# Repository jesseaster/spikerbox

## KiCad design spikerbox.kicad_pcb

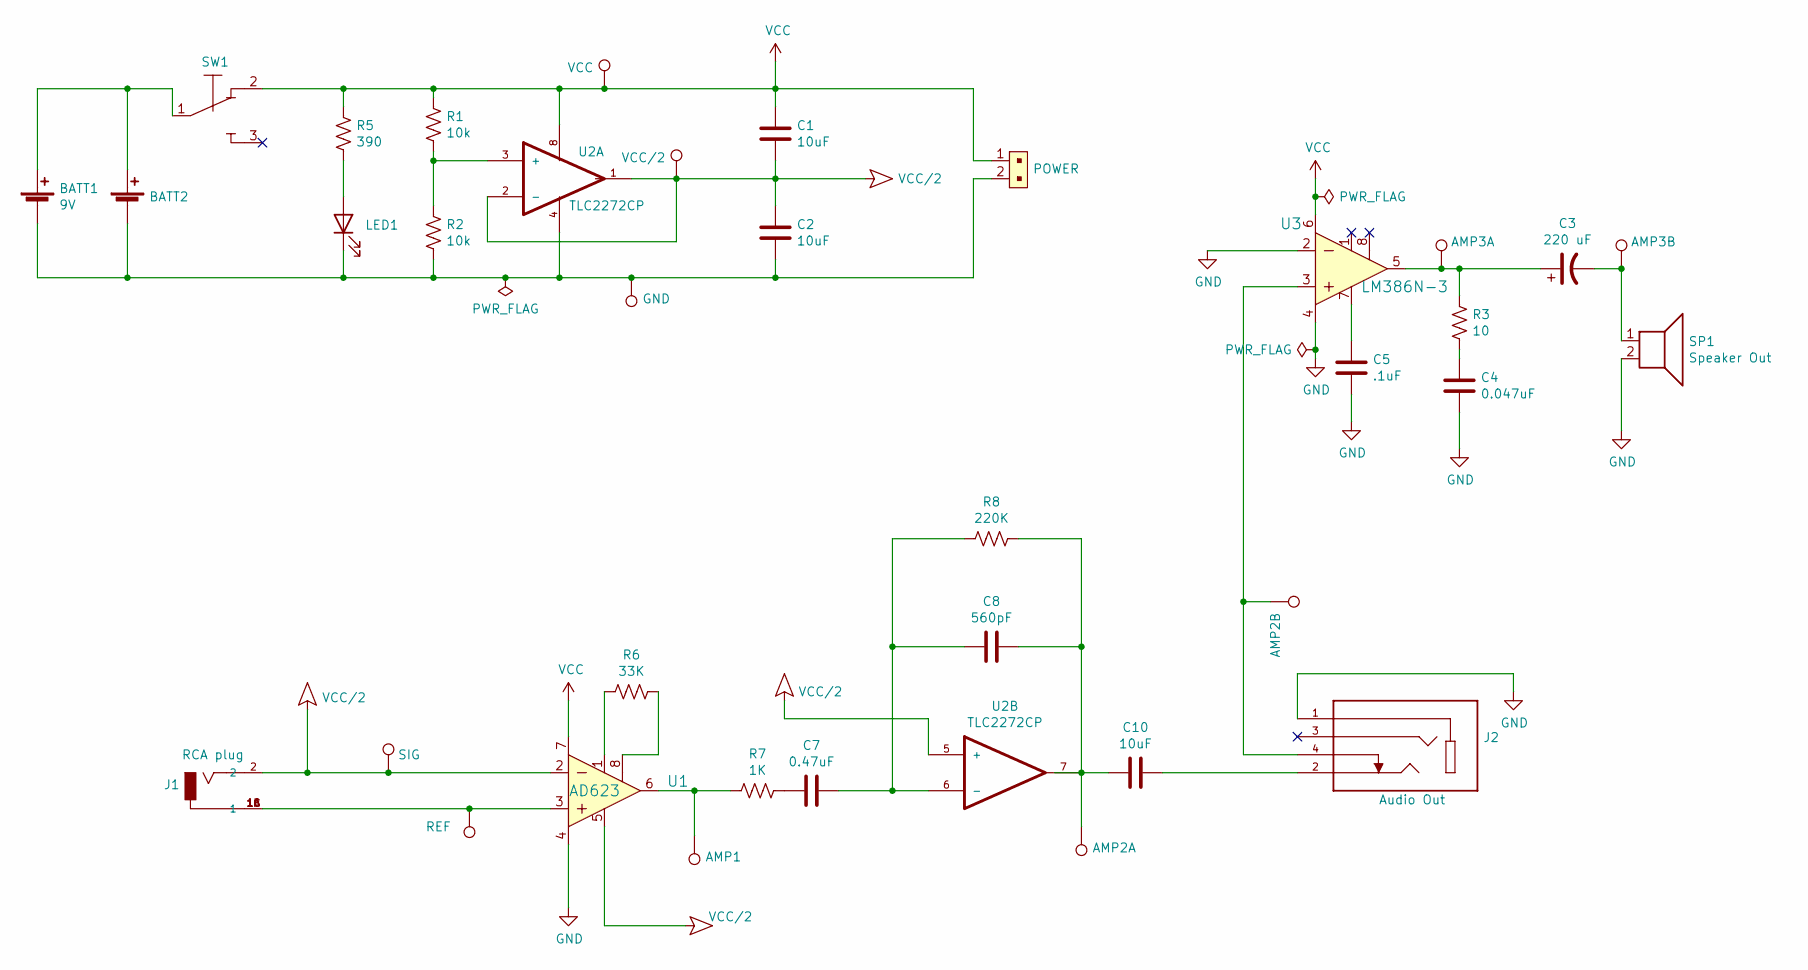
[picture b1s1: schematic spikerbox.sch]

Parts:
BATT1: 9V; 9V-Battery-Holder; Digi-Key_PN N145-ND, 593K-ND, 594K-ND
C1, C2: 10uF; C_Rect_L7.0mm_W3.5mm_P5.00mm; Digi-Key_PN 399-9805-ND
C3: 220 uF; CP_Radial_D8.0mm_P3.50mm; Digi-Key_PN 565-1674-ND
C4: 0.047uF; C_Rect_L7.0mm_W3.5mm_P5.00mm; Digi-Key_PN BC1099CT-ND
C5: .1uF; C_Rect_L4.0mm_W2.5mm_P2.50mm; Digi-Key_PN BC1148CT-ND
C7: 0.47uF; C_Rect_L7.0mm_W3.5mm_P5.00mm; Digi-Key_PN 445-175054-1-ND
C8: 560pF; C_Rect_L4.0mm_W2.5mm_P2.50mm; Digi-Key_PN BC1022CT-ND
C10: 10uF; C_Rect_L7.0mm_W3.5mm_P5.00mm; Digi-Key_PN 445-173370-1-ND
HEADER1: POWER; PinHeader_1x02_P2.54mm_Vertical; MPN 22-23-2021; Digi-Key_PN WM4200-ND
HEADER2: BATT2; PinHeader_1x02_P2.54mm_Vertical
J1: RCA plug; CUI_RCJ-014; Digi-Key_PN CP-1403-ND
J2: Audio Out; CUI_SJ1-3524NG; Digi-Key_PN CP1-3524NG-ND
LED1: LED; SSF-LXH104GD; Digi-Key_PN 67-1037-ND
R1, R2: 10k; R_Axial_DIN0207_L6.3mm_D2.5mm_P15.24mm_Horizontal; Digi-Key_PN CF14JT10K0CT-ND
R3: 10; R_Axial_DIN0207_L6.3mm_D2.5mm_P15.24mm_Horizontal; Digi-Key_PN S10QCT-ND
R5: 390; R_Axial_DIN0207_L6.3mm_D2.5mm_P15.24mm_Horizontal; Digi-Key_PN CF14JT390RCT-ND
R6: 33K; R_Axial_DIN0207_L6.3mm_D2.5mm_P15.24mm_Horizontal; Digi-Key_PN CF14JT33K0CT-ND
R7: 1K; R_Axial_DIN0207_L6.3mm_D2.5mm_P15.24mm_Horizontal; Digi-Key_PN CF14JT1K00CT-ND
R8: 220K; R_Axial_DIN0207_L6.3mm_D2.5mm_P15.24mm_Horizontal; Digi-Key_PN S220KQCT-ND
SP1: Speaker Out; PinSocket_1x02_P2.54mm_Vertical; Digi-Key_PN 102-1554-ND
SW1: 2M1-SP1-T2-B4-M6RE; Digi-Key_PN 432-1164-ND
TestPoint1: VCC; Test_Point_D1.02mm
TestPoint2: GND; Test_Point_D1.02mm
TestPoint3: VCC/2; Test_Point_D1.02mm
TestPoint4: SIG; Test_Point_D1.02mm
TestPoint5: REF; Test_Point_D1.02mm
TestPoint6: AMP1; Test_Point_D1.02mm
TestPoint7: AMP2A; Test_Point_D1.02mm
TestPoint8: AMP2B; Test_Point_D1.02mm
TestPoint9: AMP3A; Test_Point_D1.02mm
TestPoint10: AMP3B; Test_Point_D1.02mm
U1: AD623; DIP-8_W7.62mm; MPN AD623ANZ; Digi-Key_PN AD623ANZ-ND
U2: TLC2272CP; DIP-8_W7.62mm; Digi-Key_PN 296-1812-5-ND
U3: LM386N-3; DIP-8_W7.62mm; MPN LM386N-3/NOPB; Digi-Key_PN 296-43959-5-ND

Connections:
GND: C4.2, C5.2, J2.1, SP1.2, U1.4, U3.2, U3.4
HT: C1.2, C2.1, J1.2, TestPoint3.1, TestPoint4.1, U1.2, U1.5, U2.1, U2.2 (-), U2.5 (+)
unnamed: BATT1.1 (+), HEADER2.1 (+), SW1.1
unnamed: BATT1.2 (-), C2.2, HEADER1.2, HEADER2.2 (-), LED1.1 (K), R2.2, TestPoint2.1, U2.4
unnamed: C3.1, R3.1, TestPoint9.1, U3.5
unnamed: C3.2, SP1.1, TestPoint10.1
unnamed: C4.1, R3.2
unnamed: C5.1, U3.7
unnamed: C7.1, C8.2, R8.2, U2.6 (-)
unnamed: C7.2, R7.1
unnamed: C10.1, J2.2
unnamed: C8.1, C10.2, R8.1, TestPoint7.1, U2.7
unnamed: J1.1A (1), J1.1B (1), J1.1C (1), TestPoint5.1, U1.3
unnamed: J2.4, TestPoint8.1, U3.3
unnamed: LED1.2 (A), R5.2
unnamed: R1.2, R2.1, U2.3 (+)
unnamed: R6.1, U1.8
unnamed: R6.2, U1.1
unnamed: R7.2, TestPoint6.1, U1.6
VCC: C1.1, HEADER1.1, R1.1, R5.1, SW1.2, TestPoint1.1, U1.7, U2.8, U3.6

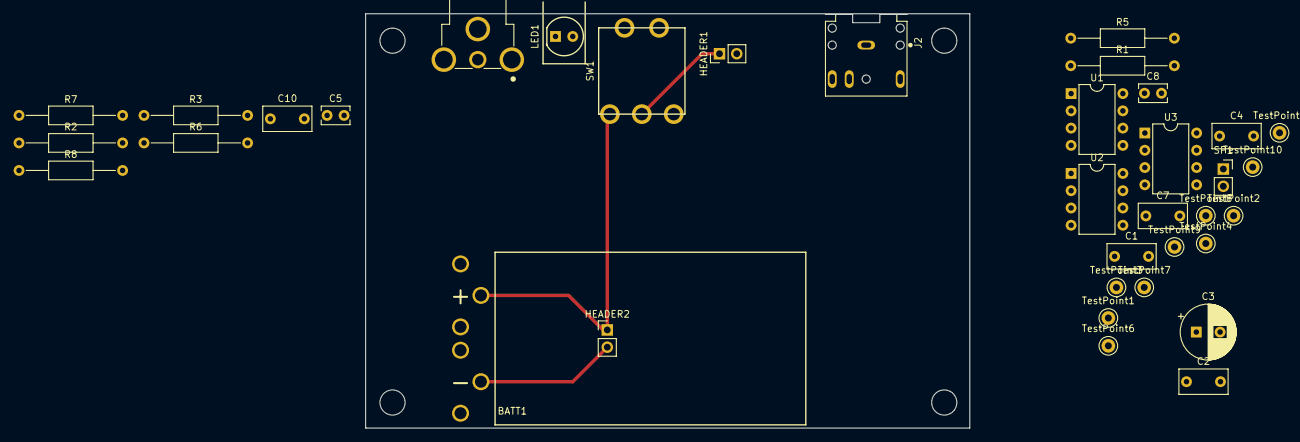
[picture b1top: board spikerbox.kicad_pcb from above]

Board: 2 copper layers, 88.9 x 61.0 mm, 36 parts (0 on the bottom side), 20 nets.

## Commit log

2020-10-15 Added gitignore
2020-10-15 Added files
